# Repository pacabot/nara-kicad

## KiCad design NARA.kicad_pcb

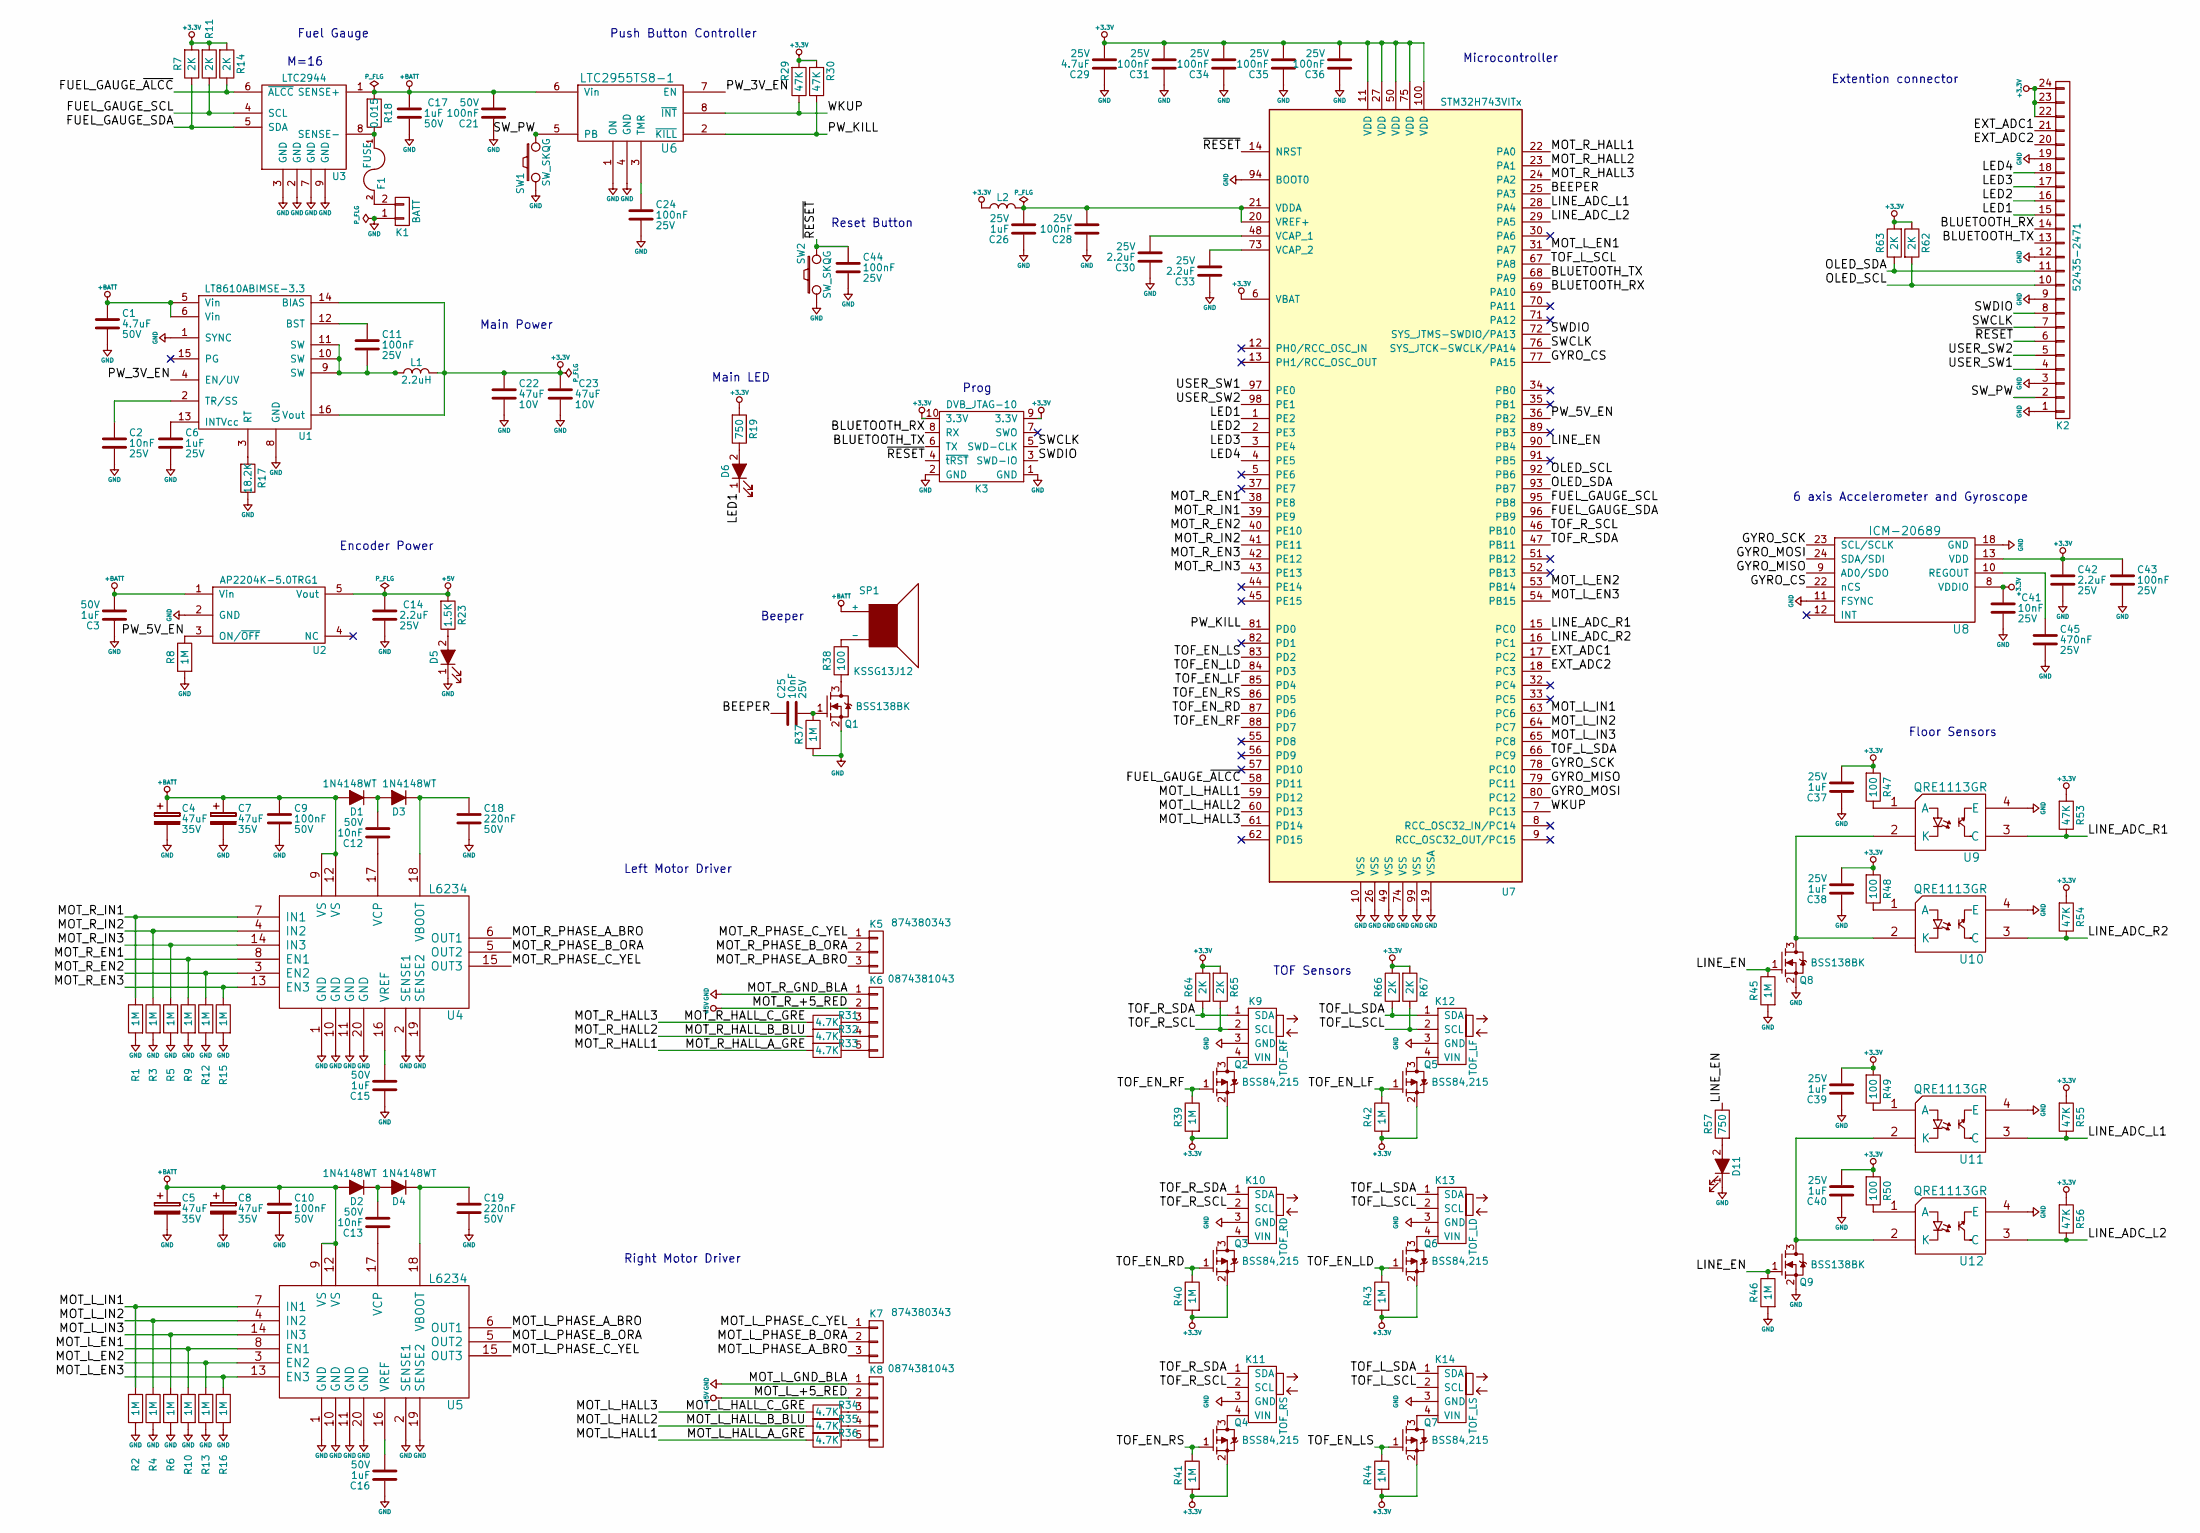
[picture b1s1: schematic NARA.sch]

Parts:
C1: C_0038; C_1206
C2, C25, C41: C_0001; C_0402
C3, C15, C16, C17: C_0056; C_0805
C4, C5, C7, C8: C_47uF; CP_EIA-7343-31
C6, C26, C37, C38, C39, C40: C_0037; C_0603
C9, C10, C21: C_0033; C_0603
C11, C24, C28, C31, C34, C35, C36, C43, C44: C_0002; C_0402
C12, C13: C_0034; C_0402
C14, C30, C33, C42: C_0045; C_0402
C18, C19: C_220nF; C_0603
C22, C23: C_0040; C_1210
C29: C_0007; C_1206
C45: C_470nF; C_0402
D1, D2, D3, D4: D_0022; D_SOD-523
D5, D6, D11: D_0001; LED_0603-red
F1: FUSE; F_1206
K1: BATT; Pin_Header_Straight_1x02_Pitch3mm
K2: K_FPC_52435-2471
K3: DVB_JTAG-10; FTSH-105-XX-X-DV
K5, K7: K_PicoSPOX-3
K6, K8: K_0002; K_PicoSPOX-5
K9: TOF_RF; GYVL53L0X
K10: TOF_RD; GYVL53L0X
K11: TOF_RS; GYVL53L0X
K12: TOF_LF; GYVL53L0X
K13: TOF_LD; GYVL53L0X
K14: TOF_LS; GYVL53L0X
L1: L_0002; L_5030-Coilcraft
L2: L_0010; L_0603
Q1, Q8, Q9: Q_0004; SOT_23
Q2, Q3, Q4, Q5, Q6, Q7: Q_0007; SOT_23
R1, R2, R3, R4, R5, R6, R8, R9, R10, R12, R13, R15, R16, R37, R39, R40, R41, R42, R43, R44, R45, R46: R_0002; R_0402
R7, R11, R14, R62, R63, R64, R65, R66, R67: R_0111; R_0402
R17: R_0030; R_0402
R18: R_0088; R_1206
R19, R57: R_0104; R_0402
R23: R_0118; R_0402
R29, R30, R53, R54, R55, R56: R_0105; R_0402
R31, R32, R33, R34, R35, R36: R_0015; R_0402
R38: R_0076; R_0603
R47, R48, R49, R50: R_0033; R_0402
SP1: SP_0001; SP_KSSG-5x5x3
SW1, SW2: SW_SKQG; SPST_SKQG
U1: U_LT8610ABIMSE-3.3; MSOP_16-1EP_3x4_P0.5
U2: U_AP2204K-5.0TRG1; SOT_23-5
U3: LTC2944; DFN_8-1EP_3x3mm_P0.5mm
U4, U5: L6234; PowerSO-20
U6: LTC2955TS8-1; SOT_23-8
U7: STM32H743VITx; LQFP-100_14x14mm_Pitch0.5mm
U8: ICM-20689; QFN-24-1EP_4x4mm_Pitch0.5mm
U9, U10, U11, U12: QRE1113GR

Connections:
+3.3V: C22.1, C23.1, C29.2, C31.2, C34.2, C35.2, C36.2, C37.2, C38.2, C39.2, C40.2, C41.1, C42.1, C43.1, K2.22, K2.23, K2.24, K3.9 (3.3V), K3.10 (3.3V), L1.2, L2.1, Q2.2 (S), Q3.2 (S), Q4.2 (S), Q5.2 (S), Q6.2 (S), Q7.2 (S), R7.1, R11.1, R14.1, R19.1, R29.1, R30.1, R39.1, R40.1, R41.1, R42.1, R43.1, R44.1, R47.1, R48.1, R49.1, R50.1, R53.1, R54.1, R55.1, R56.1, R62.2, R63.1, R64.2, R65.1, R66.2, R67.1, U1.14 (BIAS), U1.16 (Vout), U7.6 (VBAT), U7.11 (VDD), U7.27 (VDD), U7.50 (VDD), U7.75 (VDD), U7.100 (VDD), U8.8 (VDDIO), U8.13 (VDD)
+5V: C14.1, K6.2, K8.2, R23.1, U2.5 (Vout)
+BATT: C1.1, C3.2, C4.1, C5.1, C7.1, C8.1, C9.1, C10.1, C17.1, C21.2, D1.2 (A), D2.2 (A), R18.1, SP1.1 (+), U1.5 (Vin), U1.6 (Vin), U2.1 (Vin), U3.1 (SENSE+), U4.9 (VS), U4.12 (VS), U5.9 (VS), U5.12 (VS), U6.6 (Vin)
/BEEPER: C25.1, U7.25 (PA3)
/BLUETOOTH_RX: K2.14, K3.8 (RX), U7.69 (PA10)
/BLUETOOTH_TX: K2.13, K3.6 (TX), U7.68 (PA9)
/EXT_ADC1: K2.21, U7.17 (PC2)
/EXT_ADC2: K2.20, U7.18 (PC3)
/FUEL_GAUGE_SCL: R11.2, U3.4 (SCL), U7.95 (PB8)
/FUEL_GAUGE_SDA: R7.2, U3.5 (SDA), U7.96 (PB9)
/FUEL_GAUGE_~ALCC: R14.2, U3.6 (~ALCC), U7.58 (PD11)
/GYRO_CS: U7.77 (PA15), U8.22 (nCS)
/GYRO_MISO: U7.79 (PC11), U8.9 (AD0/SDO)
/GYRO_MOSI: U7.80 (PC12), U8.24 (SDA/SDI)
/GYRO_SCK: U7.78 (PC10), U8.23 (SCL/SCLK)
/LED1: D6.1 (K), K2.15, U7.1 (PE2)
/LED2: K2.16, U7.2 (PE3)
/LED3: K2.17, U7.3 (PE4)
/LED4: K2.18, U7.4 (PE5)
/LINE_ADC_L1: R55.2, U7.28 (PA4), U11.3 (C)
/LINE_ADC_L2: R56.2, U7.29 (PA5), U12.3 (C)
/LINE_ADC_R1: R53.2, U7.15 (PC0), U9.3 (C)
/LINE_ADC_R2: R54.2, U7.16 (PC1), U10.3 (C)
/LINE_EN: Q8.1 (G), Q9.1 (G), R45.2, R46.2, R57.2, U7.90 (PB4)
/MOT_L_EN1: R10.2, U5.8 (EN1), U7.31 (PA7)
/MOT_L_EN2: R13.2, U5.3 (EN2), U7.53 (PB14)
/MOT_L_EN3: R16.2, U5.13 (EN3), U7.54 (PB15)
/MOT_L_HALL1: R36.2, U7.59 (PD12)
/MOT_L_HALL2: R35.2, U7.60 (PD13)
/MOT_L_HALL3: R34.2, U7.61 (PD14)
/MOT_L_IN1: R2.2, U5.7 (IN1), U7.63 (PC6)
/MOT_L_IN2: R4.2, U5.4 (IN2), U7.64 (PC7)
/MOT_L_IN3: R6.2, U5.14 (IN3), U7.65 (PC8)
/MOT_L_PHASE_A_BRO: K7.3, U5.6 (OUT1)
/MOT_L_PHASE_B_ORA: K7.2, U5.5 (OUT2)
/MOT_L_PHASE_C_YEL: K7.1, U5.15 (OUT3)
/MOT_R_EN1: R9.2, U4.8 (EN1), U7.38 (PE8)
/MOT_R_EN2: R12.2, U4.3 (EN2), U7.40 (PE10)
/MOT_R_EN3: R15.2, U4.13 (EN3), U7.42 (PE12)
/MOT_R_HALL1: R33.2, U7.22 (PA0)
/MOT_R_HALL2: R32.2, U7.23 (PA1)
/MOT_R_HALL3: R31.2, U7.24 (PA2)
/MOT_R_IN1: R1.2, U4.7 (IN1), U7.39 (PE9)
/MOT_R_IN2: R3.2, U4.4 (IN2), U7.41 (PE11)
/MOT_R_IN3: R5.2, U4.14 (IN3), U7.43 (PE13)
/MOT_R_PHASE_A_BRO: K5.3, U4.6 (OUT1)
/MOT_R_PHASE_B_ORA: K5.2, U4.5 (OUT2)
/MOT_R_PHASE_C_YEL: K5.1, U4.15 (OUT3)
/OLED_SCL: K2.10, R62.1, U7.92 (PB6)
/OLED_SDA: K2.11, R63.2, U7.93 (PB7)
/PW_3V_EN: U1.4 (EN/UV), U6.7 (EN)
/PW_5V_EN: R8.2, U2.3 (ON/~OFF), U7.36 (PB2)
/PW_KILL: R30.2, U6.2 (~KILL), U7.81 (PD0)
/SWCLK: K2.7, K3.5 (SWD-CLK), U7.76 (SYS_JTCK-SWCLK/PA14)
/SWDIO: K2.8, K3.3 (SWD-IO), U7.72 (SYS_JTMS-SWDIO/PA13)
/SW_PW: K2.2, SW1.1, U6.5 (PB)
/TOF_EN_LD: Q6.1 (G), R43.2, U7.84 (PD3)
/TOF_EN_LF: Q5.1 (G), R42.2, U7.85 (PD4)
/TOF_EN_LS: Q7.1 (G), R44.2, U7.83 (PD2)
/TOF_EN_RD: Q3.1 (G), R40.2, U7.87 (PD6)
/TOF_EN_RF: Q2.1 (G), R39.2, U7.88 (PD7)
/TOF_EN_RS: Q4.1 (G), R41.2, U7.86 (PD5)
/TOF_L_SCL: K12.2 (SCL), K13.2 (SCL), K14.2 (SCL), R67.2, U7.67 (PA8)
/TOF_L_SDA: K12.1 (SDA), K13.1 (SDA), K14.1 (SDA), R66.1, U7.66 (PC9)
/TOF_R_SCL: K9.2 (SCL), K10.2 (SCL), K11.2 (SCL), R65.2, U7.46 (PB10)
/TOF_R_SDA: K9.1 (SDA), K10.1 (SDA), K11.1 (SDA), R64.1, U7.47 (PB11)
/USER_SW1: K2.4, U7.97 (PE0)
/USER_SW2: K2.5, U7.98 (PE1)
/WKUP: R29.2, U6.8 (~INT), U7.7 (PC13)
/~RESET: C44.1, K2.6, K3.4 (~tRST), SW2.2, U7.14 (NRST)
GND: C1.2, C2.2, C3.1, C4.2, C5.2, C6.2, C7.2, C8.2, C9.2, C10.2, C14.2, C15.1, C16.1, C17.2, C18.2, C19.2, C21.1, C22.2, C23.2, C24.2, C26.1, C28.1, C29.1, C30.1, C31.1, C33.1, C34.1, C35.1, C36.1, C37.1, C38.1, C39.1, C40.1, C41.2, C42.2, C43.2, C44.2, C45.2, D5.1 (K), D11.1 (K), K1.1, K2.1, K2.3, K2.9, K2.12, K2.19, K3.1 (GND), K3.2 (GND), K6.1, K8.1, K9.3 (GND), K10.3 (GND), K11.3 (GND), K12.3 (GND), K13.3 (GND), K14.3 (GND), Q1.2 (S), Q8.2 (S), Q9.2 (S), R1.1, R2.1, R3.1, R4.1, R5.1, R6.1, R8.1, R9.1, R10.1, R12.1, R13.1, R15.1, R16.1, R17.2, R37.1, R45.1, R46.1, SW1.2, SW2.1, U1.1 (SYNC), U1.8 (GND), U1.17 (GND), U2.2 (GND), U3.2 (GND), U3.3 (GND), U3.7 (GND), U3.9 (GND), U4.1 (GND), U4.2 (SENSE1), U4.10 (GND), U4.11 (GND), U4.19 (SENSE2), U4.20 (GND), U5.1 (GND), U5.2 (SENSE1), U5.10 (GND), U5.11 (GND), U5.19 (SENSE2), U5.20 (GND), U6.1 (ON), U6.4 (GND), U7.10 (VSS), U7.19 (VSSA), U7.26 (VSS), U7.49 (VSS), U7.74 (VSS), U7.94 (BOOT0), U7.99 (VSS), U8.11 (FSYNC), U8.18 (GND), U9.4 (E), U10.4 (E), U11.4 (E), U12.4 (E)
unnamed: C2.1, U1.2 (TR/SS)
unnamed: C6.1, U1.13 (INTVcc)
unnamed: C11.1, U1.12 (BST)
unnamed: C11.2, L1.1, U1.9 (SW), U1.10 (SW), U1.11 (SW)
unnamed: C12.1, U4.17 (VCP)
unnamed: C12.2, D1.1 (K), D3.2 (A)
unnamed: C13.1, U5.17 (VCP)
unnamed: C13.2, D2.1 (K), D4.2 (A)
unnamed: C15.2, U4.16 (VREF)
unnamed: C16.2, U5.16 (VREF)
unnamed: C18.1, D3.1 (K), U4.18 (VBOOT)
unnamed: C19.1, D4.1 (K), U5.18 (VBOOT)
unnamed: C24.1, U6.3 (TMR)
unnamed: C25.2, Q1.1 (G), R37.2
unnamed: C26.2, C28.2, L2.2, U7.20 (VREF+), U7.21 (VDDA)
unnamed: C30.2, U7.48 (VCAP_1)
unnamed: C33.2, U7.73 (VCAP_2)
unnamed: C45.1, U8.10 (REGOUT)
unnamed: D5.2 (A), R23.2
unnamed: D6.2 (A), R19.2
unnamed: D11.2 (A), R57.1
unnamed: F1.1, R18.2, U3.8 (SENSE-)
unnamed: F1.2, K1.2
unnamed: K6.3, R31.1
unnamed: K6.4, R32.1
unnamed: K6.5, R33.1
unnamed: K8.3, R34.1
unnamed: K8.4, R35.1
unnamed: K8.5, R36.1
unnamed: K9.4 (VIN), Q2.3 (D)
unnamed: K10.4 (VIN), Q3.3 (D)
unnamed: K11.4 (VIN), Q4.3 (D)
unnamed: K12.4 (VIN), Q5.3 (D)
unnamed: K13.4 (VIN), Q6.3 (D)
unnamed: K14.4 (VIN), Q7.3 (D)
unnamed: Q1.3 (D), R38.1
unnamed: Q8.3 (D), U9.2 (K), U10.2 (K)
unnamed: Q9.3 (D), U11.2 (K), U12.2 (K)
unnamed: R17.1, U1.3 (RT)
unnamed: R38.2, SP1.2 (-)
unnamed: R47.2, U9.1 (A)
unnamed: R48.2, U10.1 (A)
unnamed: R49.2, U11.1 (A)
unnamed: R50.2, U12.1 (A)

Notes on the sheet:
M=16
Microcontroller
Prog
Beeper
Left Motor Driver
Right Motor Driver
Main Power
Encoder Power
TOF Sensors
Floor Sensors
6 axis Accelerometer and Gyroscope
Reset Button
Fuel Gauge
Push Button Controller
Extention connector
Main LED

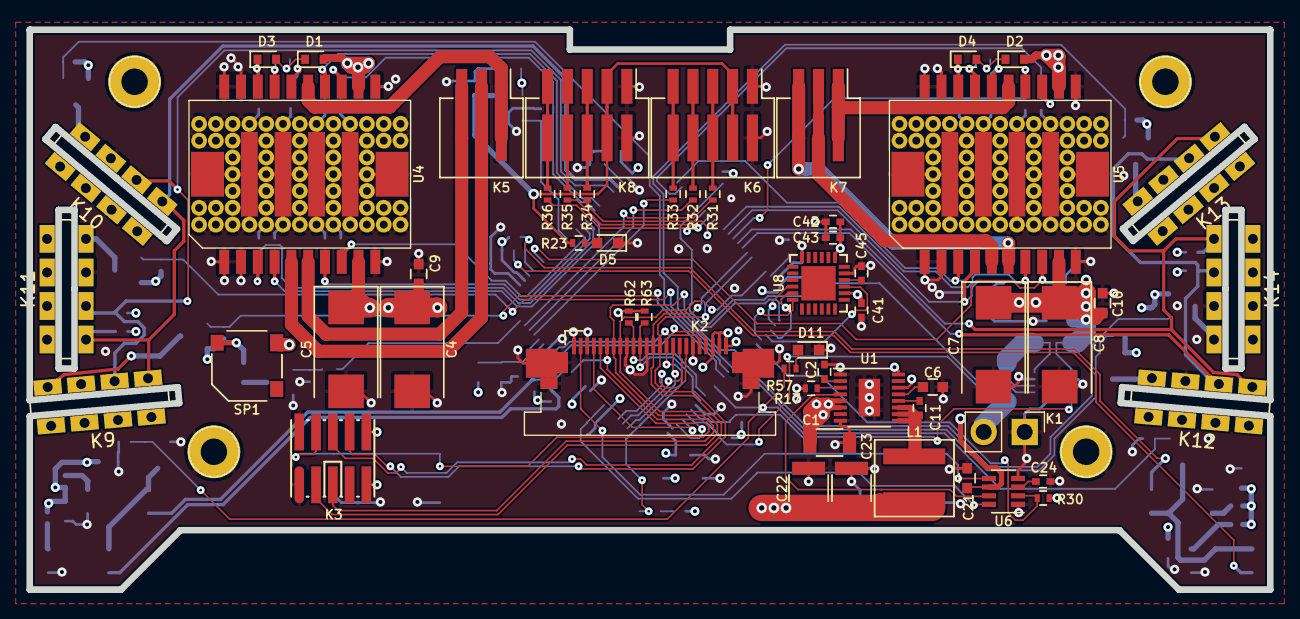
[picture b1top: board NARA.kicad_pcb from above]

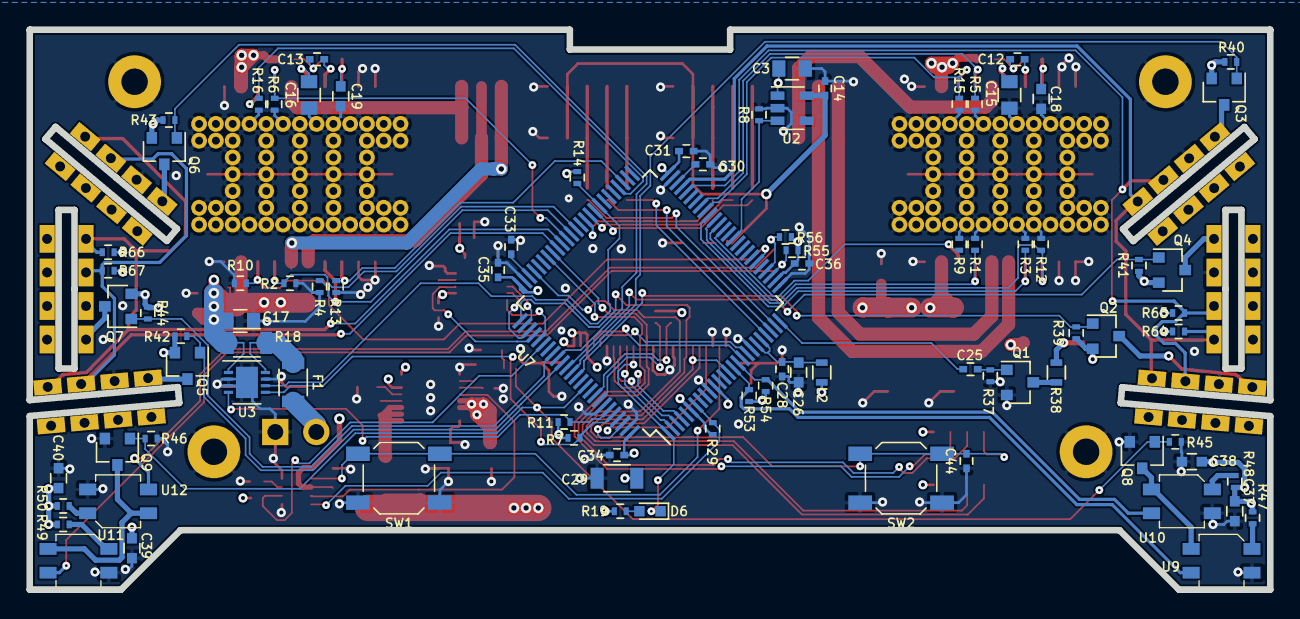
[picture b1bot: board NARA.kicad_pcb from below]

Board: 4 copper layers, 93.9 x 42.4 mm, 142 parts (86 on the bottom side), 115 nets.

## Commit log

2018-04-07 First commit all files added
2018-04-07 split kicad and CubeMX project (move to eclipse project)
2018-04-07 Update schematic
2018-04-08 First schematic version
2018-04-08 Add NARA_Lib.pretty
2018-04-09 Update footprints, prepare to place composants
2018-04-15 First components placement, Autoroute in progress
2018-04-17 Add GND and PWR layer
2018-04-18 Change EdgeCuts for TOF sensors, adapt power trace lengh
2018-04-19 Save before change vias
2018-04-19 Update via type, route Top, GND, PWR complete
2018-04-21 First NARA PCB, v1.0.0-B1
2018-04-21 New v1.1.0, add jtag Connector and main led
2018-04-21 Generate gerbers, first eurocircuit purpose
2018-04-22 Update Gerbers (clean errors for Eurocircuit)
2018-04-23 Mouve debug connector
2018-04-23 Change PCB sensors footprint
2018-04-25 Eurocircuit v1.1.0-B1
2018-04-25 Reduce TOF sensor footprint
2018-04-25 In this version, we trust
